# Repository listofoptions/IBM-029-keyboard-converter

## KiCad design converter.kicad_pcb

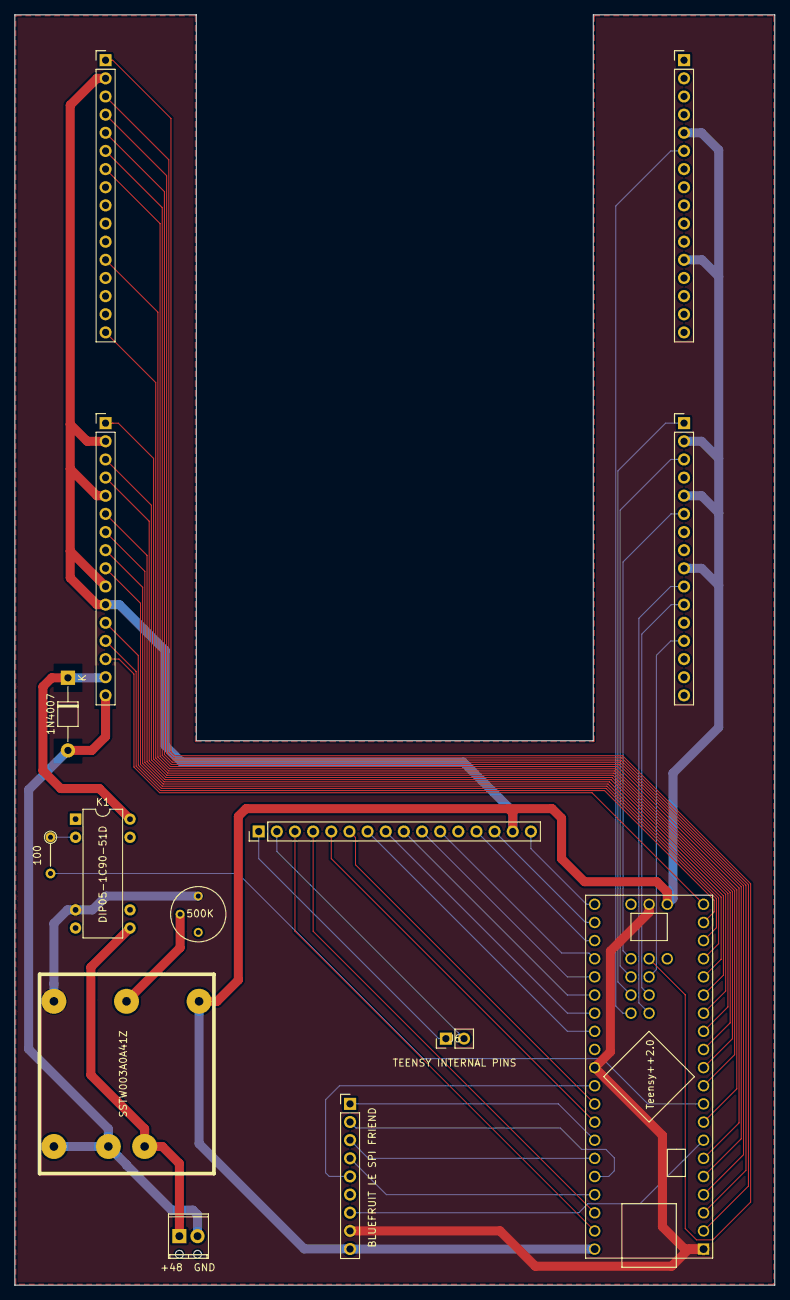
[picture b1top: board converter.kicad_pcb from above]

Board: 2 copper layers, 106.4 x 177.8 mm, 14 parts (0 on the bottom side), 53 nets.

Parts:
D1: 1N4007; D_T-1_P10.16mm_Horizontal
J1: A04; Pin_Header_Straight_1x16_Pitch2.54mm
J2: B08; Pin_Header_Straight_1x16_Pitch2.54mm
J3: A01; Pin_Header_Straight_1x16_Pitch2.54mm
J4: A02; Pin_Header_Straight_1x16_Pitch2.54mm
J5: A03; Pin_Header_Straight_1x16_Pitch2.54mm
J6: TEENSY INTERNAL PINS; Pin_Header_Straight_1x02_Pitch2.54mm
J7: +48 GND; TerminalBlock_Phoenix_MPT-2.54mm_2pol
J8: BLUEFRUIT LE SPI FRIEND; Pin_Header_Straight_1x09_Pitch2.54mm
K1: DIP05-1C90-51D
R2: 100; R_Axial_DIN0204_L3.6mm_D1.6mm_P5.08mm_Vertical
RV1: 500K; Potentiometer_Trimmer_Bourns_3339P_Horizontal
U1: SSTW003A0A41Z
U2: Teensy++2.0; Teensy2.0++

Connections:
+5VD: J1.15, J2.5, J2.12, J3.2, J3.5, J3.9, J4.2, J5.2, J5.5, J5.10, J5.11, J8.9, U1.6, U2.21, U2.43
+48V: J7.1, K1.8, U1.1
-48V: D1.2, J5.16, J7.2, U1.2, U1.3
/ALPHA: J5.13, U2.19
/AUTO_DUP: J3.6, U2.47
/AUTO_FEED: J3.1, U2.45
/AUX_DUP: J4.5, U2.4
/BAIL_8: J4.6, U2.5
/BAIL_9: J1.16, U2.24
/C0: J1.4, U2.41
/C1: J1.5, U2.36
/C2: J1.6, U2.35
/C3: J1.7, U2.31
/C4: J1.8, U2.30
/C5: J1.9, U2.29
/C6: J1.10, U2.28
/C7: J1.11, U2.27
/C9: J1.13, U2.26
/C11: J1.3, U2.42
/C12: J1.2, J6.2
/CLEAR: J3.10, U2.48
/DASH_SKIP: J4.12, U2.8
/DUP: J5.9, U2.17
/ERROR_RESET: J1.14, U2.25
/FEED: J5.6, U2.14
/INT_PCH: J2.6, U2.44
/IRQ: J8.5, U2.34
/LEFT_ZERO: J4.3, U2.2
/LZ_PRINT: J3.13, U2.50
/MC: J4.4, U2.3
/MISO: J8.2, U2.39
/MOSI: J8.3, U2.38
/MULTI_O: J5.12, U2.18
/NUM+MULTI_I: J5.14, U2.20
/PRINT: J3.11, U2.49
/PROG_1: J4.7, U2.6
/PROG_2: J5.8, U2.16
/PROG_SEL: J3.3, U2.46
/R0: J5.3, U2.12
/R1: J5.4, U2.13
/REGISTER_LATCH: J5.7, U2.15
/REL: J4.16, U2.10
/RESET: J8.7, U2.7
/RESTORE: J5.1, U2.11
/RESTORE_MAGS: R2.2, U2.9
/SCLK: J8.1, U2.37
/SKIP: J4.1, U2.51
/SPACE: J1.1, J6.1
/~CS: J8.4, U2.40
GNDD: J8.8, K1.6, RV1.3, U1.4, U2.1, U2.22, U2.33
unnamed: D1.1, J5.15, K1.14
unnamed: K1.2, R2.1
unnamed: RV1.2, U1.5

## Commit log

2019-06-24 removing plots
2019-06-24 missed some stuff
2019-06-24 forgot even more stuff
2019-06-24 forgot to bump versions
2019-06-24 added back slik screen labels for assembly assistance
2019-06-28 various varigations verified vicariously, verily verbose
2019-06-28 updated flyback diode footprint, and cleaned up some of the silkscreening
2019-06-28 fixed an obvious missing pad clearance on the restore magnet
